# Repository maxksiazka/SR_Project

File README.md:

# SR_Project
## Autonomous Robotic ENgineered Takedown Machine
---
### Opis projektu

Projekt obejmuje zrealizowanie mobilnego robota typu [mini-sumo](https://kcir.pwr.edu.pl/~mucha/Pracki/Michal_Piotrowicz_praca_inzynierska.pdf).
Mechanika projektu znajduje się w podfolderze *Mechanics/*, podczas gdy projekt KiCad elektroniki układu znajduje się w podfolderze *Electronics/*.
Oprogramowanie robota mobilnego znajduje się w podfolderze *sumo/*.

---

### Elementy składowe robota

- MCU: **Raspberry Pi Pico 2 WH**
- Time-of-Flight Sensor: **VL53L0X**
- Czujnik odbiciowy: **KTIR0711S**
- Sterownik silników (H-bridge): **TB6612FNG**
- Silniki: **N20-BT37 micro X:1**
- Moduł Wi-Fi: zintegrowany z MCU.
- Zasilanie: **Li-Po 2S**

---

### Zadania projektowe 

**Kolejność na liście zadań nie jest wiążąca.**
 - [x] Wykonanie wstępnego projektu mechaniki robota.
 - [x] Wykonanie projektu elektroniki robota.
 - [x] Zakup elementów elektronicznych.
 - [x] Wydrukowanie wstępnego korpusu robota.
 - [x] Wydrukowanie wstępnych kół robota
 - [x] Napisanie prostego klienta TCP - 'echo'.
 - [x] Napisanie systemu kontroli silników - kontrola PWM.
 - [x] Napisanie prostego systemu sterowania: klient TCP -> PWM.
 - [x] Implementacja odbioru danych z TOF - komunikacja I^2^C.
 - [x] Implementacja odbioru danych z czujników odbiciowych - ADC.
 - [x] Implementacja autonomicznego systemu sterowania
 - [ ] (Opcjonalnie, ale prawie na pewno) Refactoring kodu.
 - [x] Finalizacja projektu korpusu.
 - [x] Finalizacja projektu kół.
 - [x] Pożar robota
 - [ ] Integracja robota.
 ---
 ---

## Metodyka Pracy
Pracujemy z użyciem `git branch` - PROSŻĘ

Standardowo merge request po *weryfikacji dwuosobowej*.

Coś jak [tutaj](https://www.geeksforgeeks.org/git/best-git-practices-to-follow-in-teams/) jeżeli chodzi o zasady to by była moja propozycja.

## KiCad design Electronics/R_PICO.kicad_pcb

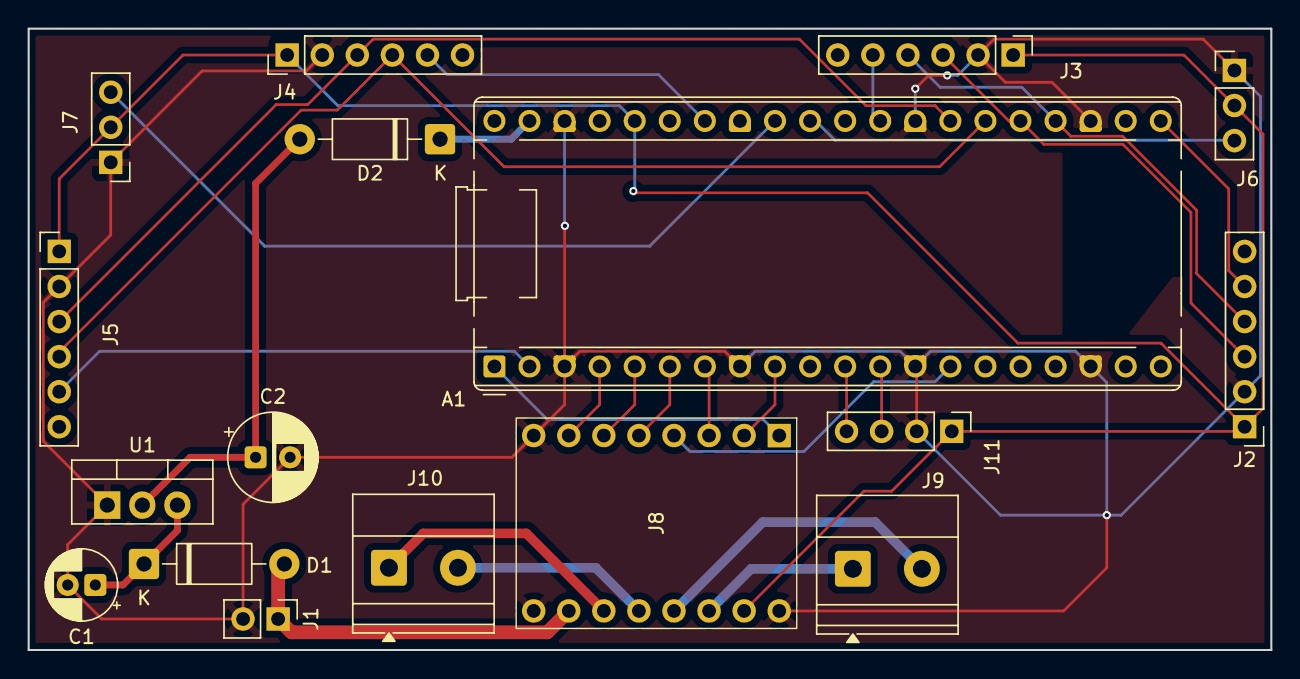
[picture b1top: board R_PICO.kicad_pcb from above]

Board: 2 copper layers, 90.0 x 45.0 mm, 17 parts (0 on the bottom side), 29 nets.

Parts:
A1: RaspberryPi_Pico_W; RaspberryPi_Pico_Common_THT
C1: 10u; CP_Radial_D5.0mm_P2.00mm
C2: 100u; CP_Radial_D6.3mm_P2.50mm
D1, D2: 1N5819; D_DO-41_SOD81_P10.16mm_Horizontal
J1: Battery_Connector; PinHeader_1x02_P2.54mm_Vertical
J2, J3, J4, J5: VL53L0X; PinHeader_1x06_P2.54mm_Vertical
J6, J7: KTIR0711S; PinHeader_1x03_P2.54mm_Vertical
J8: TB6612FNG; TB6612FNG_Polulu_Breakout
J9: MotorL; TerminalBlock_Phoenix_MKDS-1,5-2_1x02_P5.00mm_Horizontal
J10: MotorR; TerminalBlock_Phoenix_MKDS-1,5-2_1x02_P5.00mm_Horizontal
J11: Starter; PinHeader_1x04_P2.54mm_Vertical
U1: LM1117T-5.0; TO-220-3_Vertical

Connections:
/2S: D1.2 (A), J1.1 (BAT+), J8.10 (VMOT)
/3V3: A1.36 (3V3), J2.1 (VCC), J3.1 (VCC), J4.1 (VCC), J5.1 (VCC), J6.2 (VCC), J7.2 (VCC), J8.15 (VCC), J11.1 (VCC)
/5V: C2.1, D2.2 (A), U1.2 (VO)
/A1: A1.7 (GPIO5), J8.3 (AIN1)
/A2: A1.9 (GPIO6), J8.2 (AIN2)
/ADC0: A1.31 (GPIO26_ADC0), J6.3 (OUT)
/ADC1: A1.32 (GPIO27_ADC1), J7.3 (OUT)
/B1: A1.6 (GPIO4), J8.5 (BIN1)
/B2: A1.5 (GPIO3), J8.6 (BIN2)
/GP10: A1.14 (GPIO10), J8.4 (STBY)
/KILL: A1.11 (GPIO8), J11.4 (KILL)
/MOT1_IN: J8.14 (AO1), J9.1
/MOT1_OUT: J8.13 (AO2), J9.2
/MOT2_IN: J8.11 (BO1), J10.1
/MOT2_OUT: J8.12 (BO2), J10.2
/PWM0A: A1.1 (GPIO0), J8.1 (PWMA)
/PWM1A: A1.4 (GPIO2), J8.7 (PWMB)
/SCL1: A1.25 (GPIO19), J2.3 (SCL), J3.3 (SCL)
/SDA1: A1.24 (GPIO18), J2.4 (SDA), J3.4 (SDA)
/START: A1.12 (GPIO9), J11.3 (START)
/XSHUT_FRONT_LEFT: A1.34 (GPIO28_ADC2), J4.5 (XSHUT)
/XSHUT_FRONT_RIGHT: A1.29 (GPIO22), J3.5 (XSHUT)
/XSHUT_LEFT: A1.2 (GPIO1), J5.5 (XSHUT)
/XSHUT_RIGHT: A1.21 (GPIO16), J2.5 (XSHUT)
/out: A1.39 (VSYS), D2.1 (K)
/scl0: A1.27 (GPIO21), J4.3 (SCL), J5.3 (SCL)
/sda0: A1.26 (GPIO20), J4.4 (SDA), J5.4 (SDA)
GND: A1.3 (GND), A1.8 (GND), A1.13 (GND), A1.18 (GND), A1.23 (GND), A1.28 (GND), A1.38 (GND), C1.2, C2.2, J1.2 (BAT-), J2.2 (GND), J3.2 (GND), J4.2 (GND), J5.2 (GND), J6.1 (GND), J7.1 (GND), J8.8 (GND), J8.9 (GND), J8.16 (GND), J11.2 (GND), U1.1 (GND)
unnamed: C1.1, D1.1 (K), U1.3 (VI)

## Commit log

2025-10-07 Extending README with project details and methodology
2025-10-07 Fix markdown link syntax in README.md
2025-10-07 Update README with line breaks
    Updated breaks between lines in README.md
2025-10-21 Initialized codebase
2025-11-16 Added mechanical schemes.
2025-11-18 Modified CMakeLists.txt to include wifi libraries, created lwipopts.h, configured for TCP/IP implementation (raw API) created inc/tcp.h, added conditional symbols for wifi configuration and TCP serve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
2025-11-18 expanded inc/tcp.h - added necessary function definitions
2025-11-18 expanded src/tcp.c - implemented init_wifi connection()
2025-11-18 expanded src/tcp.c - implemented tcp_client_init()
2025-11-18 expanded src/tcp.c - implemented tcp_client_open_connection(), created skeleton callback implementations(TODO: Implement); expanded inc/tcp.h - changed variable names to avoid conflict, corrected err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
2025-11-18 mechanics/fix
2025-11-22 renamed tcp.c and tcp.h, modified .gitignore and added compile options to CMake
2025-11-22 added tcp_recv_callback implementation (unfinished - call to handler),added tcp_handling.c/tcp_handling.h, implemented echo function,modified CMakeLists with new filenames
2025-11-22 modified: CMakeLists.txt modified: inc/lwipopts.h modified: inc/tcp_api_implementation.h modified: inc/tcp_handling.h new file: inc/tcp_typedefs.h modified: src/main.c modified: src/tcp_api_implement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
2025-11-22 Revert bad commit
    This reverts commit 1a5bd893fcc986c2d9f44336ead459a8e4bed94c.
2025-11-22 modified: CMakeLists.txt - Added new files modified: inc/lwipopts.h - used lwipopts_examples_common from pico-examples modified: inc/tcp_api_implementation.h - added print debugging modified: inc/tcp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
2025-11-23 Substituted printf calls with DEBUG_printf macro
2025-11-23 modified: CMakeLists.txt - Added compiler options, modified: inc/main.h - extracted LED_PIN and DEBUG_printf definitions, modified: inc/tcp_typedefs.h - forrmatting, modified: src/tcp_api_implementat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
2025-11-23 modified: CMakeLists.txt - removed incompatible compiler options
    modified: inc/tcp_typedefs.h - forrmatted
    modified: src/main.c - Tried to implement termination - client gets
    freed, and thats it
    modified: src/tcp_api_implementation.c - implemented send
    callback,modified close function
2025-11-23 modified: .gitignore - added vscode modified: sumo/inc/tcp_typedefs.h - changed to my router config modified: sumo/src/tcp_api_implementation.c - added error_callback
2025-11-23 modified: sumo/src/tcp_api_implementation.c - added connection callback and fixed error callback debug print
2025-11-23 Update tcp_api_implementation.c
    Removed redundant things
2025-11-23 modified: sumo/inc/tcp_typedefs.h - added new commands modified: sumo/src/tcp_typedefs.c - defined new commands
2025-11-30 Dodano projekt elektroniki, zaktualizowano README.md
2025-11-30 Created initialization of pwm modules, added new files to CMakeLists.txt
2025-11-30 added basic control system - unfinished
2025-11-30 Disabled compiler optimization, added simple forward/stop movement
2025-11-30 simple control of motor over TCP/IP
2025-11-30 added build instructions
2025-11-30 Update README.md
    Updated README with project progress.
2025-11-30 Update motor specification from 210:1 to 200:1
2025-12-12 Removed hardcoded wifi definitions in favor of system variables
2025-12-12 added some i2c things for tof handle
2025-12-12 missing files
2025-12-12 fixed CMake, abandoned static library project
2025-12-12 corrected electronic schema, added adc support
2025-12-12 suit for multiple tof
2025-12-19 Changed name of VL53L0X_pico_lib to libVL53L0X_pico, changed compilation type to actually be a static library
2025-12-19 changed misspelt name: LICENCE.txt -> LICENSE.txt
2025-12-19 refactored to a static library, updated to proper licensing, updated library README.md
2025-12-28 Completed VL53L0X initalization.
2026-01-06 Changed filenames to adhere to code.
2026-01-06 added helper defines to pwm_motor_control, added pivot functions to tcp_handling
2026-01-06 fixed missing directions in pwm_motor_control
2026-01-06 added additional control functions
2026-01-06 Added a few control functions
2026-01-10 Fix copyright notice in LICENSE.txt
2026-01-16 preparations for control work
2026-01-16 Control loop finished, only tuning left
2026-01-16 added starter scheme
2026-01-24 edited control
2026-01-24 updated electronics
2026-01-25 stage III mechanics
2026-02-10 FIX: Changed Electronics schema
    Changed footprints of VL53L0X, KTIRs, and TB6612FNG. Amended electronics
    schema to match breakout boards.
    TODO: PCB schematic
2026-02-10 Feat: Finished PCB schematic, awaiting fabrication decision
2026-02-10 Update motor specification and project tasks
